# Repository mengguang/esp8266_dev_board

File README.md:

# esp8266_dev_board
esp8266 development board
The number of GPIO are not enough for some development, so I added a PCF8574 GPIO Expander IC on the development board.

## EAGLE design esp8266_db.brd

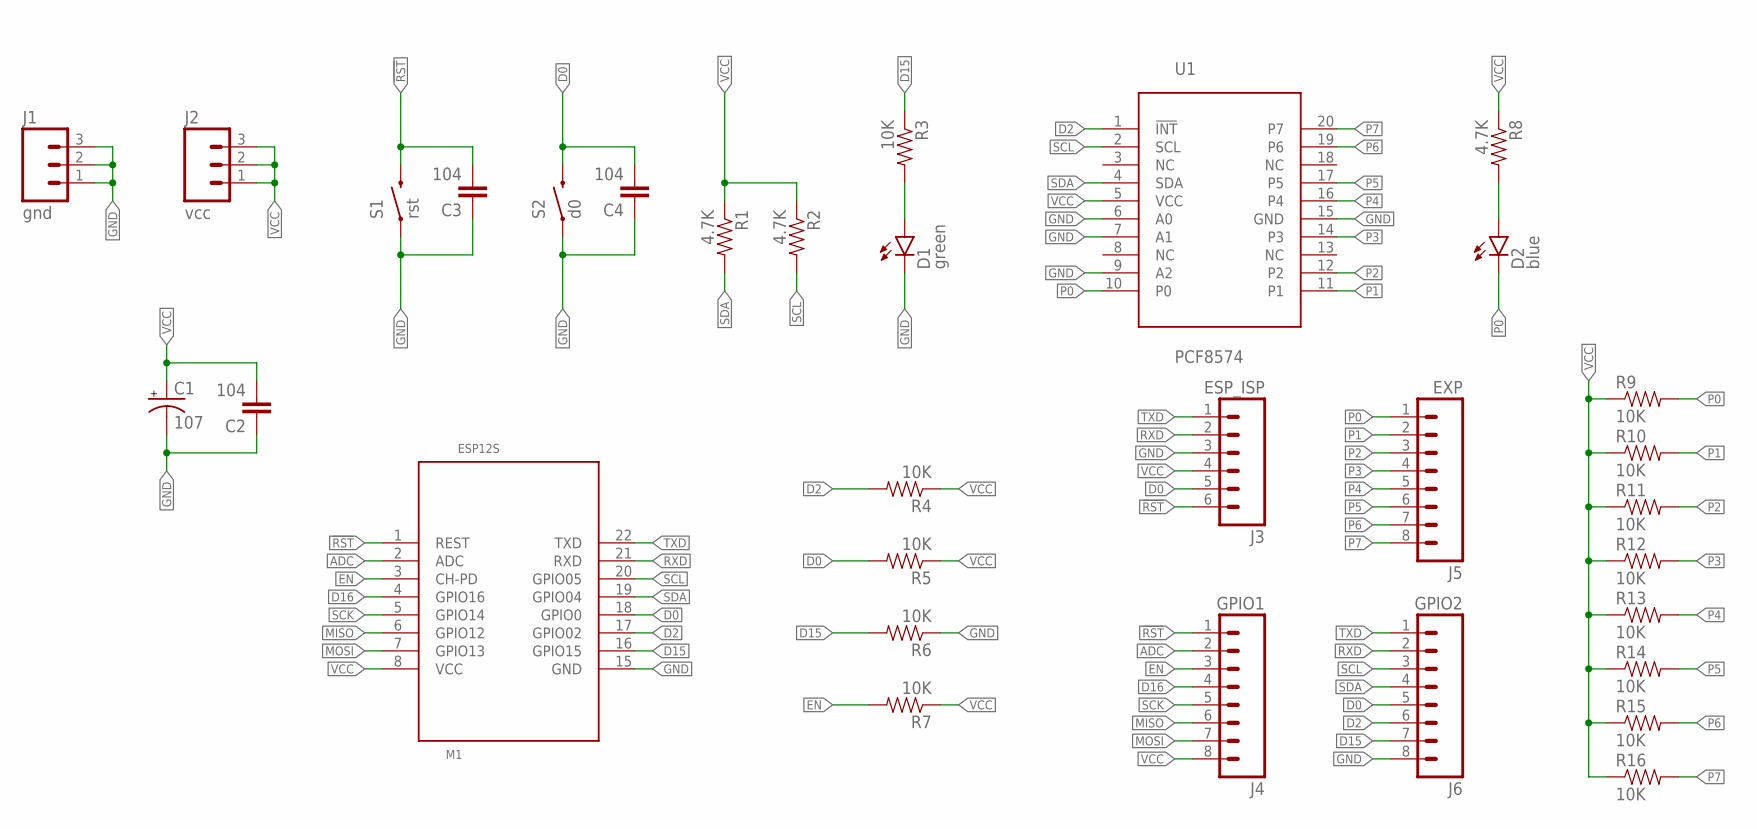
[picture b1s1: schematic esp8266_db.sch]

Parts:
C1: 107; EIA3528
C2, C3, C4: 104; 0603-CAP
D1: green; LED-0603-EASY
D2: blue; LED-0603-EASY
J1: gnd; 1X03_NO_SILK
J2: vcc; 1X03_NO_SILK
J3: ESP_ISP; 1X06_NO_SILK
J4: GPIO1; 1X08_NO_SILK
J5: EXP; 1X08_NO_SILK
J6: GPIO2; 1X08_NO_SILK
M1: ESP12S; LGA22-2.0-24X16MM-SIMPLE
R1, R2, R8: 4.7K; 0603-RES
R3, R4, R5, R6, R7, R9, R10, R11, R12, R13, R14, R15, R16: 10K; 0603-RES
S1: rst; TACTILE-PTH
S2: d0; TACTILE-PTH
U1: PCF8574; TSSOP20

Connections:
!RST: C3.2, J3.6, J4.1, M1.1 (REST), S1.3 (2)
ADC: J4.2, M1.2 (ADC)
D0: C4.2, J3.5, J6.5, M1.18 (GPIO0), R5.2, S2.3 (2)
D2: J6.6, M1.17 (GPIO02), R4.2, U1.1 (!INT)
D15: J6.7, M1.16 (GPIO15), R3.1, R6.2
D16: J4.4, M1.4 (GPIO16)
EN: J4.3, M1.3 (CH-PD), R7.2
GND: C1.C (-), C2.1, C3.1, C4.1, D1.- (C), J1.1, J1.2, J1.3, J3.3, J6.8, M1.15 (GND), R6.1, S1.1, S2.1, U1.6 (A0), U1.7 (A1), U1.9 (A2), U1.15 (GND)
MISO: J4.6, M1.6 (GPIO12)
MOSI: J4.7, M1.7 (GPIO13)
unnamed: D2.+ (A), R8.2
unnamed: D1.+ (A), R3.2
P0: D2.- (C), J5.1, R9.2, U1.10 (P0)
P1: J5.2, R10.2, U1.11 (P1)
P2: J5.3, R11.2, U1.12 (P2)
P3: J5.4, R12.2, U1.14 (P3)
P4: J5.5, R13.2, U1.16 (P4)
P5: J5.6, R14.2, U1.17 (P5)
P6: J5.7, R15.2, U1.19 (P6)
P7: J5.8, R16.2, U1.20 (P7)
RXD: J3.2, J6.2, M1.21 (RXD)
SCK: J4.5, M1.5 (GPIO14)
SCL: J6.3, M1.20 (GPIO05), R2.2, U1.2 (SCL)
SDA: J6.4, M1.19 (GPIO04), R1.2, U1.4 (SDA)
TXD: J3.1, J6.1, M1.22 (TXD)
VCC: C1.A (+), C2.2, J2.1, J2.2, J2.3, J3.4, J4.8, M1.8 (VCC), R1.1, R2.1, R4.1, R5.1, R7.1, R8.1, R9.1, R10.1, R11.1, R12.1, R13.1, R14.1, R15.1, R16.1, U1.5 (VCC)

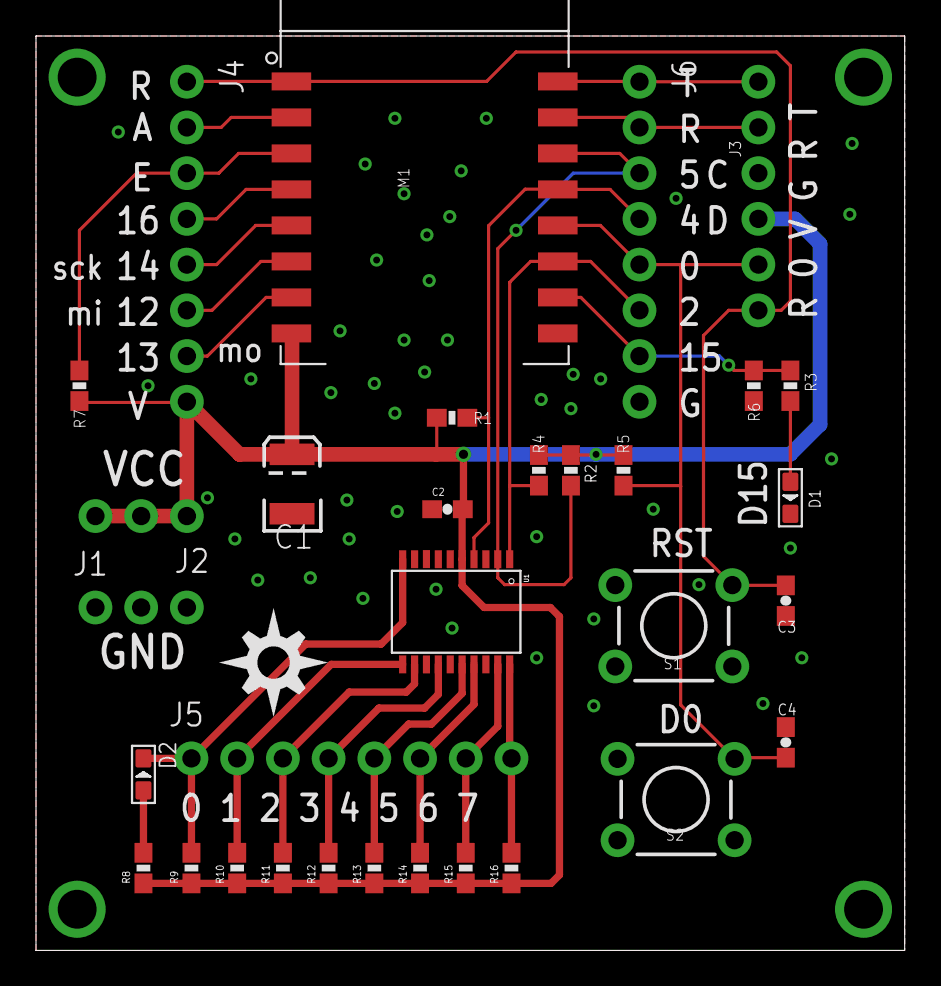
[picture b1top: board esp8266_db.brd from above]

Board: 2 copper layers, 48.3 x 50.8 mm, 33 parts (0 on the bottom side), 26 nets.

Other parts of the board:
U$1: DIYNOVA_LOGO

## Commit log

2017-11-02 version 2

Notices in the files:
parts and their libraries:
SparkFun-Connectors: Licensing: Creative Commons ShareAlike 4.0 International - https://creativecommons.org/licenses/by-sa/4.0
